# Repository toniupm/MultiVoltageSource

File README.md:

# MultiVoltageSource

<b> Design and Programming by Antonio Perez-Serrano </b> 

<b> PCB Design by Jose David Ayala </b> 

<i> CEMDATIC - ETSI Telecomunicación, Universidad Politécnica de Madrid (UPM) </i>

Version 1.0 - December 2020

<p align="justify"> Here we describe the MultiVoltageSource project, a voltage source with 7 channels used to power up photonic integrated circuits. </p>

<p align="justify">
     The <b> hardware </b> is based on negative linear regulators <a href="https://www.analog.com/en/products/lt3090.html#product-overview" target="_blank">LT3090</a> and digital potentiometers <a href="https://www.analog.com/en/products/ad5290.html" target="_blank">AD5290</a> controlled by an Arduino Nano <a href="https://store.arduino.cc/arduino-nano-every" target="_blank">Every</a> or <a href="https://store.arduino.cc/arduino-nano-33-iot" target="_blank">33 IOT</a>. It offers 7 channels ranging from -0.2 V to -10.2 V. A power supply of &plusmn; 15 V or &plusmn; 12 V is needed. The current output of the power supply must be choosen depending on the application, in our case a current output of 0.5 A is enough. The schematics and PCB design have been created using <a href="https://kicad.org/" target="_blank">KiCad</a> and they can be found in the <i> Kicad Project </i> folder. The MultiVoltageSource box has been designed using <a href="https://www.blender.org/" target="_blank">Blender</a>, it can be found in the <i> Blender Project </i> folder. The box can be 3D printed using PLA or ABS material and it is designed to use M3 bolts and nuts. The MultiVoltageSource is controlled via serial port, this allows to program voltage sweeps easily.   
</p>

<p align="justify">
     The list of the materials used are:
     <ul>
          <li> 1 Arduino Nano <a href="https://store.arduino.cc/arduino-nano-every" target="_blank">Every</a> or <a href="https://store.arduino.cc/arduino-nano-33-iot" target="_blank">33 IOT</a> </li>
          <li> 7 chips <a href="https://www.analog.com/en/products/lt3090.html#product-overview" target="_blank">LT3090</a> </li>
          <li> 14 chips <a href="https://www.analog.com/en/products/ad5290.html" target="_blank">AD5290</a> </li>
          <li> 1 LCD display 20x4 characters </li>
          <li> 1 i2c/SPI LCD backpack <a href="https://learn.adafruit.com/i2c-spi-lcd-backpack" target="_blank">i2c/SPI LCD backpack</a> with the SPI enabled </li>
          <li> 1 Embedded Linear Power Supply Encapsulated PS2127 &plusmn; 15 V</li>
          <li> 1 Voltage Regulator to 5 V LD1085V50 </li>
          <li> 7 Resistors 2k &#8486; </li>
          <li> 7 Resistors 2.2k &#8486; </li>
          <li> 7 Resistors 10k &#8486; </li>
          <li> 7 Capacitors 4.7 uF </li>
          <li> 2 Capacitors 10 uF </li>
          <li> 14 Capacitors 100 nF </li>
          <li> Several PCB connectors including 1 <a href="https://www.samtec.com/products/fcs8-20-01-l-s-a-tr" target="_blank">FCS8-20-01-L-S-A-TR</a> connector </li>
          <li> 1 Switch </li>
          <li> 1 Button </li>
          <li> 1 Power Supply cable and connector </li>
          <li> Several cables </li>
     </ul>          
</p>

The cost of a MultiVoltage source is around 200 €.

<p align="justify">
     The <b> software </b> can be found in the <i> Software </i> folder. It contains the Arduino Firmware and the LabVIEW project and functions to control the MultiVoltageSource. LabVIEW 2020 version has been used to create the controlling software. At this moment, only serial communication through a USB cable is supported. Next versions will include WiFi communication.   
</p>

<p align="justify">
     Future improvements/changes:
          <ul>
               <li> WiFi communication using Arduino Nano 33 IOT </li>
               <li> Creation a stand-alone control software based on Processing </li>
          </ul>     
</p>

<p align="justify">
We acknowledge support from Comunidad de Madrid through project MULTI-GAS-PIC (APOYO-JOVENES-KXHJ8C-16-VCKM78) and Ministerio de Ciencia e Innovación of Spain through project LIDERA (RTI2018-094118-B-C21).
</p>

<p align="justify">
"Acción financiada por la Comunidad de Madrid en el marco del Convenio Plurianual con la Universidad Politécnica de Madrid <b> en la línea de actuación estímulo a la investigación de jóvenes doctores </b>"
</p>

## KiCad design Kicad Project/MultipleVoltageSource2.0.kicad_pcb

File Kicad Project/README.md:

This folder contains the KiCad project of the MultiVoltageSource, including schematics, PCB and final Gerber files.

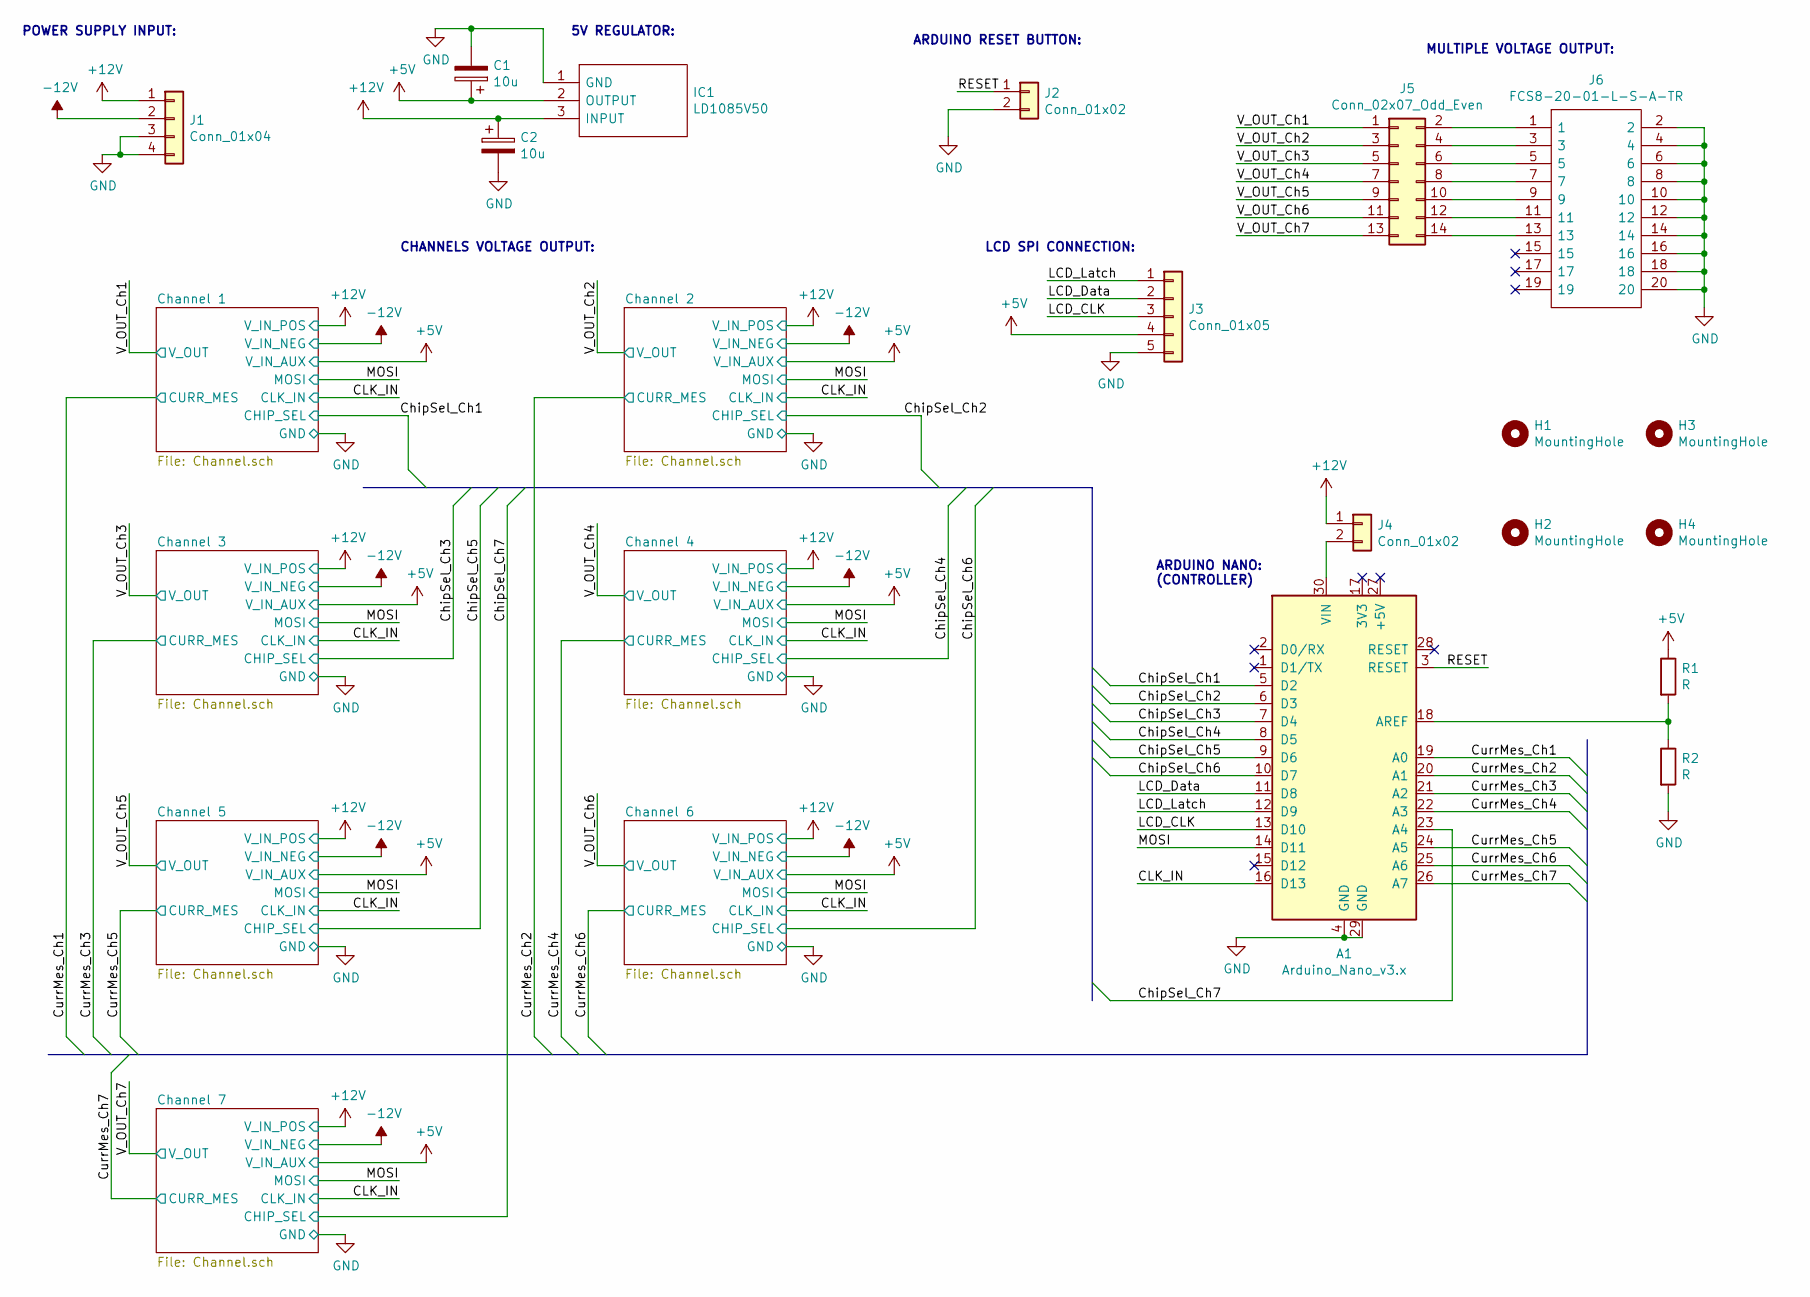
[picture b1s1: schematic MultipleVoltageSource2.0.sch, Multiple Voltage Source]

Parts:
A1: Arduino_Nano_v3.x; Arduino_Nano
C1, C2: 10u; CP_Radial_Tantal_D5.0mm_P2.50mm
H1, H2, H3, H4: MountingHole; MountingHole_3.2mm_M3
IC1: LD1085V50; TO270P460X1020X2008-3P; Mouser Part Number 511-LD1085V50
J1: Conn_01x04; SHDR4W100P0X500_1X4_2000X800X1000P
J2, J4: Conn_01x02; PinHeader_1x02_P2.54mm_Vertical
J3: Conn_01x05; PinHeader_1x05_P2.54mm_Vertical
J5: Conn_02x07_Odd_Even; PinHeader_2x07_P2.54mm_Vertical
J6: FCS8-20-01-L-S-A-TR; FCS8-20-01-X-S-A; Mouser Part Number 200-FCS82001LSATR
R1, R2: R; R_Axial_DIN0204_L3.6mm_D1.6mm_P7.62mm_Horizontal

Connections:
+5V: C1.1, IC1.2 (OUTPUT), J3.4, R1.1; also elsewhere on the board
+12V: C2.1, IC1.3 (INPUT), J1.1, J4.1; also elsewhere on the board
-12V: J1.2; also elsewhere on the board
/CLK_IN: A1.16 (D13); also elsewhere on the board
/ChipSel_Ch1: A1.5 (D2); also elsewhere on the board
/ChipSel_Ch2: A1.6 (D3); also elsewhere on the board
/ChipSel_Ch3: A1.7 (D4); also elsewhere on the board
/ChipSel_Ch4: A1.8 (D5); also elsewhere on the board
/ChipSel_Ch5: A1.9 (D6); also elsewhere on the board
/ChipSel_Ch6: A1.10 (D7); also elsewhere on the board
/ChipSel_Ch7: A1.23 (A4); also elsewhere on the board
/CurrMes_Ch1: A1.19 (A0); also elsewhere on the board
/CurrMes_Ch2: A1.20 (A1); also elsewhere on the board
/CurrMes_Ch3: A1.21 (A2); also elsewhere on the board
/CurrMes_Ch4: A1.22 (A3); also elsewhere on the board
/CurrMes_Ch5: A1.24 (A5); also elsewhere on the board
/CurrMes_Ch6: A1.25 (A6); also elsewhere on the board
/CurrMes_Ch7: A1.26 (A7); also elsewhere on the board
/LCD_CLK: A1.13 (D10), J3.3
/LCD_Data: A1.11 (D8), J3.2
/LCD_Latch: A1.12 (D9), J3.1
/MOSI: A1.14 (D11); also elsewhere on the board
/RESET: A1.3 (RESET), J2.1
/V_OUT_Ch1: J5.1; also elsewhere on the board
/V_OUT_Ch2: J5.3; also elsewhere on the board
/V_OUT_Ch3: J5.5; also elsewhere on the board
/V_OUT_Ch4: J5.7; also elsewhere on the board
/V_OUT_Ch5: J5.9; also elsewhere on the board
/V_OUT_Ch6: J5.11; also elsewhere on the board
/V_OUT_Ch7: J5.13; also elsewhere on the board
GND: A1.4 (GND), A1.29 (GND), C1.2, C2.2, IC1.1 (GND), J1.3, J1.4, J2.2, J3.5, J6.2, J6.4, J6.6, J6.8, J6.10, J6.12, J6.14, J6.16, J6.18, J6.20, R2.2; also elsewhere on the board
unnamed: A1.18 (AREF), R1.2, R2.1
unnamed: A1.30 (VIN), J4.2
unnamed: J5.2, J6.1
unnamed: J5.4, J6.3
unnamed: J5.6, J6.5
unnamed: J5.8, J6.7
unnamed: J5.10, J6.9
unnamed: J5.12, J6.11
unnamed: J5.14, J6.13

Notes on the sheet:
POWER SUPPLY INPUT:
LCD SPI CONNECTION:
MULTIPLE VOLTAGE OUTPUT:
ARDUINO NANO: (CONTROLLER)
CHANNELS VOLTAGE OUTPUT:
5V REGULATOR:
ARDUINO RESET BUTTON:

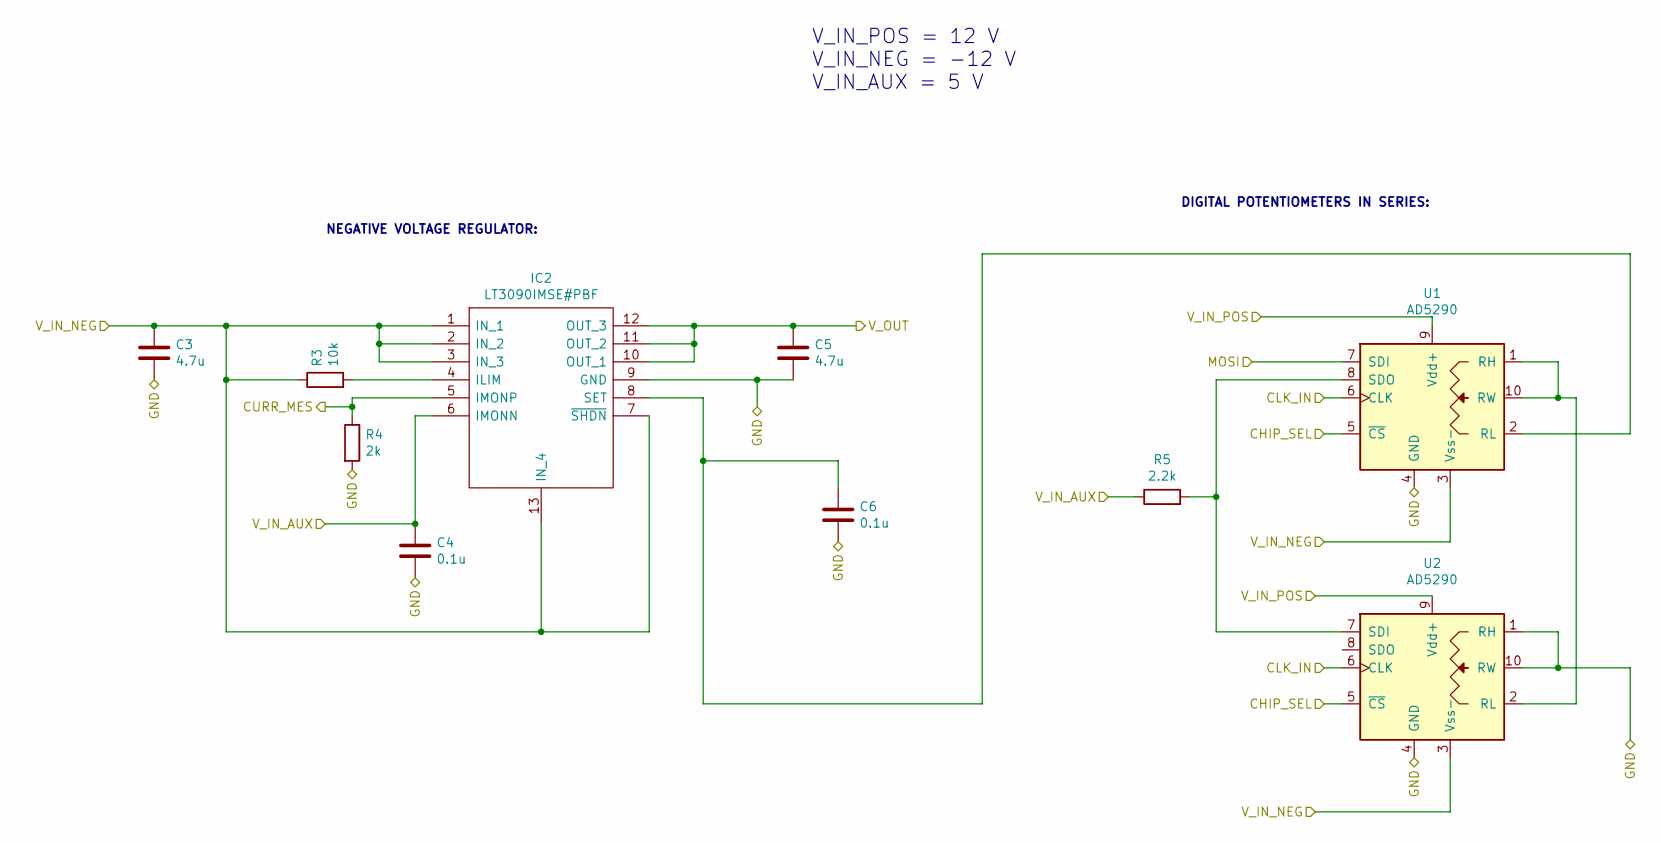
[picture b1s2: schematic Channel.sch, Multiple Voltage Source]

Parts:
C3, C5: 4.7u; C_Disc_D5.0mm_W2.5mm_P5.00mm
C4, C6: 0.1u; C_Disc_D5.0mm_W2.5mm_P5.00mm
IC2: LT3090IMSE#PBF; MSOP-12-1EP_3x4mm_P0.65mm_EP1.65x2.85mm; Manufacturer_Part_Number LT3090IMSE#PBF
R3: 10k; R_Axial_DIN0204_L3.6mm_D1.6mm_P7.62mm_Horizontal
R4: 2k; R_Axial_DIN0204_L3.6mm_D1.6mm_P7.62mm_Horizontal
R5: 2.2k; R_Axial_DIN0204_L3.6mm_D1.6mm_P7.62mm_Horizontal
U1, U2: AD5290; MSOP-10_3x3mm_P0.5mm

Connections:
+5V: C4.1, IC2.6 (IMONN), R5.1; also elsewhere on the board
+12V: U1.9 (Vdd+), U2.9 (Vdd+); also elsewhere on the board
-12V: C3.1, IC2.1 (IN_1), IC2.2 (IN_2), IC2.3 (IN_3), IC2.7 (~SHDN), IC2.13 (IN_4), R3.1, U1.3 (Vss-), U2.3 (Vss-); also elsewhere on the board
/CLK_IN: U1.6 (CLK), U2.6 (CLK); also elsewhere on the board
/ChipSel_Ch1: U1.5 (~CS~), U2.5 (~CS~); also elsewhere on the board
/CurrMes_Ch1: IC2.5 (IMONP), R4.1; also elsewhere on the board
/MOSI: U1.7 (SDI); also elsewhere on the board
/V_OUT_Ch1: C5.1, IC2.10 (OUT_1), IC2.11 (OUT_2), IC2.12 (OUT_3); also elsewhere on the board
GND: C3.2, C4.2, C5.2, C6.2, IC2.9 (GND), R4.2, U1.4 (GND), U2.1 (RH), U2.4 (GND), U2.10 (RW); also elsewhere on the board
unnamed: C6.1, IC2.8 (SET), U1.2 (RL)
unnamed: IC2.4 (ILIM), R3.2
unnamed: R5.2, U1.8 (SDO), U2.7 (SDI)
unnamed: U1.1 (RH), U1.10 (RW), U2.2 (RL)

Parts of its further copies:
C7, C9, C11, C13, C15, C17, C19, C21, C23, C25, C27, C29: 4.7u; C_Disc_D5.0mm_W2.5mm_P5.00mm
C8, C10, C12, C14, C16, C18, C20, C22, C24, C26, C28, C30: 0.1u; C_Disc_D5.0mm_W2.5mm_P5.00mm
IC3, IC4, IC5, IC6, IC7, IC8: LT3090IMSE#PBF; MSOP-12-1EP_3x4mm_P0.65mm_EP1.65x2.85mm; Manufacturer_Part_Number LT3090IMSE#PBF
R6, R9, R12, R15, R18, R21: 10k; R_Axial_DIN0204_L3.6mm_D1.6mm_P7.62mm_Horizontal
R7, R10, R13, R16, R19, R22: 2k; R_Axial_DIN0204_L3.6mm_D1.6mm_P7.62mm_Horizontal
R8, R11, R14, R17, R20, R23: 2.2k; R_Axial_DIN0204_L3.6mm_D1.6mm_P7.62mm_Horizontal
U3, U4, U5, U6, U7, U8, U9, U10, U11, U12, U13, U14: AD5290; MSOP-10_3x3mm_P0.5mm

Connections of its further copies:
+5V: C8.1, C12.1, C16.1, C20.1, C24.1, C28.1, IC3.6 (IMONN), IC4.6 (IMONN), IC5.6 (IMONN), IC6.6 (IMONN), IC7.6 (IMONN), IC8.6 (IMONN), R8.1, R11.1, R14.1, R17.1, R20.1, R23.1; also elsewhere on the board
+12V: U3.9 (Vdd+), U4.9 (Vdd+), U5.9 (Vdd+), U6.9 (Vdd+), U7.9 (Vdd+), U8.9 (Vdd+), U9.9 (Vdd+), U10.9 (Vdd+), U11.9 (Vdd+), U12.9 (Vdd+), U13.9 (Vdd+), U14.9 (Vdd+); also elsewhere on the board
-12V: C7.1, C11.1, C15.1, C19.1, C23.1, C27.1, IC3.1 (IN_1), IC3.2 (IN_2), IC3.3 (IN_3), IC3.7 (~SHDN), IC3.13 (IN_4), IC4.1 (IN_1), IC4.2 (IN_2), IC4.3 (IN_3), IC4.7 (~SHDN), IC4.13 (IN_4), IC5.1 (IN_1), IC5.2 (IN_2), IC5.3 (IN_3), IC5.7 (~SHDN), IC5.13 (IN_4), IC6.1 (IN_1), IC6.2 (IN_2), IC6.3 (IN_3), IC6.7 (~SHDN), IC6.13 (IN_4), IC7.1 (IN_1), IC7.2 (IN_2), IC7.3 (IN_3), IC7.7 (~SHDN), IC7.13 (IN_4), IC8.1 (IN_1), IC8.2 (IN_2), IC8.3 (IN_3), IC8.7 (~SHDN), IC8.13 (IN_4), R6.1, R9.1, R12.1, R15.1, R18.1, R21.1, U3.3 (Vss-), U4.3 (Vss-), U5.3 (Vss-), U6.3 (Vss-), U7.3 (Vss-), U8.3 (Vss-), U9.3 (Vss-), U10.3 (Vss-), U11.3 (Vss-), U12.3 (Vss-), U13.3 (Vss-), U14.3 (Vss-); also elsewhere on the board
/CLK_IN: U3.6 (CLK), U4.6 (CLK), U5.6 (CLK), U6.6 (CLK), U7.6 (CLK), U8.6 (CLK), U9.6 (CLK), U10.6 (CLK), U11.6 (CLK), U12.6 (CLK), U13.6 (CLK), U14.6 (CLK); also elsewhere on the board
/ChipSel_Ch2: U3.5 (~CS~), U4.5 (~CS~); also elsewhere on the board
/ChipSel_Ch3: U5.5 (~CS~), U6.5 (~CS~); also elsewhere on the board
/ChipSel_Ch4: U7.5 (~CS~), U8.5 (~CS~); also elsewhere on the board
/ChipSel_Ch5: U9.5 (~CS~), U10.5 (~CS~); also elsewhere on the board
/ChipSel_Ch6: U11.5 (~CS~), U12.5 (~CS~); also elsewhere on the board
/ChipSel_Ch7: U13.5 (~CS~), U14.5 (~CS~); also elsewhere on the board
/CurrMes_Ch2: IC3.5 (IMONP), R7.1; also elsewhere on the board
/CurrMes_Ch3: IC4.5 (IMONP), R10.1; also elsewhere on the board
/CurrMes_Ch4: IC5.5 (IMONP), R13.1; also elsewhere on the board
/CurrMes_Ch5: IC6.5 (IMONP), R16.1; also elsewhere on the board
/CurrMes_Ch6: IC7.5 (IMONP), R19.1; also elsewhere on the board
/CurrMes_Ch7: IC8.5 (IMONP), R22.1; also elsewhere on the board
/MOSI: U3.7 (SDI), U5.7 (SDI), U7.7 (SDI), U9.7 (SDI), U11.7 (SDI), U13.7 (SDI); also elsewhere on the board
/V_OUT_Ch2: C9.1, IC3.10 (OUT_1), IC3.11 (OUT_2), IC3.12 (OUT_3); also elsewhere on the board
/V_OUT_Ch3: C13.1, IC4.10 (OUT_1), IC4.11 (OUT_2), IC4.12 (OUT_3); also elsewhere on the board
/V_OUT_Ch4: C17.1, IC5.10 (OUT_1), IC5.11 (OUT_2), IC5.12 (OUT_3); also elsewhere on the board
/V_OUT_Ch5: C21.1, IC6.10 (OUT_1), IC6.11 (OUT_2), IC6.12 (OUT_3); also elsewhere on the board
/V_OUT_Ch6: C25.1, IC7.10 (OUT_1), IC7.11 (OUT_2), IC7.12 (OUT_3); also elsewhere on the board
/V_OUT_Ch7: C29.1, IC8.10 (OUT_1), IC8.11 (OUT_2), IC8.12 (OUT_3); also elsewhere on the board
GND: C7.2, C8.2, C9.2, C10.2, C11.2, C12.2, C13.2, C14.2, C15.2, C16.2, C17.2, C18.2, C19.2, C20.2, C21.2, C22.2, C23.2, C24.2, C25.2, C26.2, C27.2, C28.2, C29.2, C30.2, IC3.9 (GND), IC4.9 (GND), IC5.9 (GND), IC6.9 (GND), IC7.9 (GND), IC8.9 (GND), R7.2, R10.2, R13.2, R16.2, R19.2, R22.2, U3.4 (GND), U4.1 (RH), U4.4 (GND), U4.10 (RW), U5.4 (GND), U6.1 (RH), U6.4 (GND), U6.10 (RW), U7.4 (GND), U8.1 (RH), U8.4 (GND), U8.10 (RW), U9.4 (GND), U10.1 (RH), U10.4 (GND), U10.10 (RW), U11.4 (GND), U12.1 (RH), U12.4 (GND), U12.10 (RW), U13.4 (GND), U14.1 (RH), U14.4 (GND), U14.10 (RW); also elsewhere on the board
unnamed: C10.1, IC3.8 (SET), U3.2 (RL)
unnamed: C14.1, IC4.8 (SET), U5.2 (RL)
unnamed: C18.1, IC5.8 (SET), U7.2 (RL)
unnamed: C22.1, IC6.8 (SET), U9.2 (RL)
unnamed: C26.1, IC7.8 (SET), U11.2 (RL)
unnamed: C30.1, IC8.8 (SET), U13.2 (RL)
unnamed: IC3.4 (ILIM), R6.2
unnamed: IC4.4 (ILIM), R9.2
unnamed: IC5.4 (ILIM), R12.2
unnamed: IC6.4 (ILIM), R15.2
unnamed: IC7.4 (ILIM), R18.2
unnamed: IC8.4 (ILIM), R21.2
unnamed: R8.2, U3.8 (SDO), U4.7 (SDI)
unnamed: R11.2, U5.8 (SDO), U6.7 (SDI)
unnamed: R14.2, U7.8 (SDO), U8.7 (SDI)
unnamed: R17.2, U9.8 (SDO), U10.7 (SDI)
unnamed: R20.2, U11.8 (SDO), U12.7 (SDI)
unnamed: R23.2, U13.8 (SDO), U14.7 (SDI)
unnamed: U3.1 (RH), U3.10 (RW), U4.2 (RL)
unnamed: U5.1 (RH), U5.10 (RW), U6.2 (RL)
unnamed: U7.1 (RH), U7.10 (RW), U8.2 (RL)
unnamed: U9.1 (RH), U9.10 (RW), U10.2 (RL)
unnamed: U11.1 (RH), U11.10 (RW), U12.2 (RL)
unnamed: U13.1 (RH), U13.10 (RW), U14.2 (RL)

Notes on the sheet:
V_IN_POS = 12 V V_IN_NEG = -12 V V_IN_AUX = 5 V
NEGATIVE VOLTAGE REGULATOR:
DIGITAL POTENTIOMETERS IN SERIES:

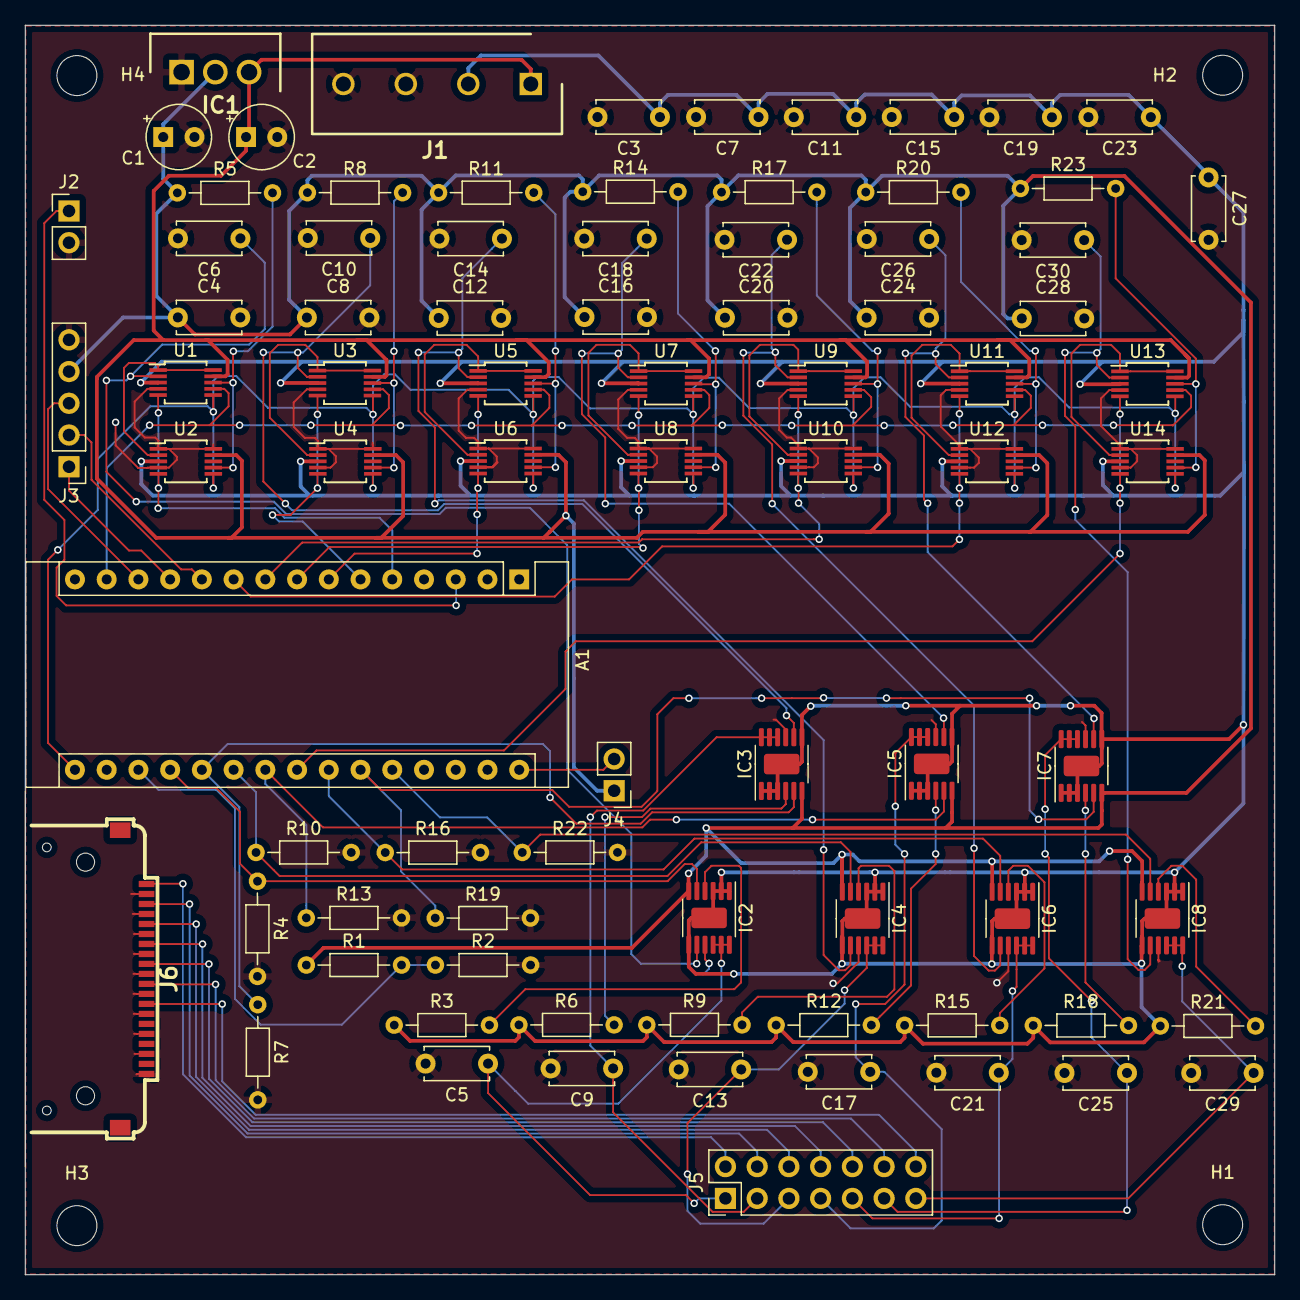
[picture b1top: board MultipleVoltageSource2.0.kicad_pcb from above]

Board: 2 copper layers, 100.0 x 100.0 mm, 86 parts (0 on the bottom side), 68 nets.

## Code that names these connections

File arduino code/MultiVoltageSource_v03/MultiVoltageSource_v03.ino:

// ******************************************************
// Multiple Voltage Source v0.3
// 31 de Julio 2020
// Author: Antonio Perez-Serrano, CEMDATIC-ETSIT (UPM)
// ******************************************************

// include libraries
#include <SPI.h>
#include "Wire.h"
#include "Adafruit_LiquidCrystal.h"

// LCD Connected via SPI
Adafruit_LiquidCrystal lcd(8, 10, 9);

// Chip Select Pins for the Different Channels
const int ChipSelect_Ch1 = 2;
const int ChipSelect_Ch2 = 3;
const int ChipSelect_Ch3 = 4;
const int ChipSelect_Ch4 = 5;
const int ChipSelect_Ch5 = 6;
const int ChipSelect_Ch6 = 7;
const int ChipSelect_Ch7 = A4;

// Current Measurement Pins for the Different Channels
const int CurrMes_Ch1 = A0;
const int CurrMes_Ch2 = A1;
const int CurrMes_Ch3 = A2;
const int CurrMes_Ch4 = A3;
const int CurrMes_Ch5 = A5;
const int CurrMes_Ch6 = A6;
const int CurrMes_Ch7 = A7;

// Other variables
String received;
int channel = 1;
int received_value;
long aux_int = 0;
int vec_valuesR[] = {0,0,0,0,0,0,0};
int vec_valuesI[] = {0,0,0,0,0,0,0};

// include our functions file
#include "functions.h"

// *********************************************
// SETUP
// *********************************************
void setup() {

  // set up the LCD's number of rows and columns: 
  lcd.begin(20, 4);
  // Print a message to the LCD.
  lcd.setCursor(4, 0);
  lcd.print("CEMDATIC-UPM");
  lcd.setCursor(0, 1);
  lcd.print("MultiVoltSource v0.3");
  lcd.setCursor(6, 2);
  lcd.print("Welcome!");
  lcd.setCursor(0, 3);
  lcd.print("starting...");
  
  // Chip Select Pins initialize:
  pinMode(ChipSelect_Ch1, OUTPUT);
  pinMode(ChipSelect_Ch2, OUTPUT);
  pinMode(ChipSelect_Ch3, OUTPUT);
  pinMode(ChipSelect_Ch4, OUTPUT);
  pinMode(ChipSelect_Ch5, OUTPUT);
  pinMode(ChipSelect_Ch6, OUTPUT);
  pinMode(ChipSelect_Ch7, OUTPUT);
  // Setting all Chip Select Pins to HIGH
  digitalWrite(ChipSelect_Ch1, HIGH);
  digitalWrite(ChipSelect_Ch2, HIGH);
  digitalWrite(ChipSelect_Ch3, HIGH);
  digitalWrite(ChipSelect_Ch4, HIGH);
  digitalWrite(ChipSelect_Ch5, HIGH);
  digitalWrite(ChipSelect_Ch6, HIGH);
  digitalWrite(ChipSelect_Ch7, HIGH);
  
  // Serial begin
  Serial.begin(1000000);
  // initialize SPI
  SPI.begin();

  for (channel=1; channel<8; channel++){ 
    digitalPotWrite(channel, vec_valuesR[channel-1]);
  }
  delay(2000);

  // First current reading
  readCurrent();
  
  // Ready message
  lcd.clear();
  lcd.setCursor(0, 1);
  lcd.print("Ready!");
  lcd.setCursor(0, 2);
  lcd.print("waiting serial...");
  
  delay(2000);
  
}

// *********************************************
// LOOP
// *********************************************
void loop() {

    Serial.flush();

    aux_int++;
    
    while ( Serial.available() > 0 ){
      received =  Serial.readStringUntil('$');

      Serial.println(received.length());
      
      channel = received.substring(0,1).toInt();
      vec_valuesR[channel-1] = received.substring(2,received.length()).toInt();
      
      Serial.println(channel);
      Serial.println(received);
      
      if (received_value >= 0 & received_value < 511){
        digitalPotWrite(channel, vec_valuesR[channel-1]); 
        displayLCD(vec_valuesR, vec_valuesI);
      } else {
        Serial.println("No valid");
      }
                
    }

    if ( aux_int == 200000 ){
      readCurrent(); 
      aux_int = 0;
      displayLCD(vec_valuesR, vec_valuesI);
    }
    

}

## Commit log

2020-12-06 Create LICENSE
2020-12-06 Create fp-info-cache
2020-12-06 Create sym-lib-table
